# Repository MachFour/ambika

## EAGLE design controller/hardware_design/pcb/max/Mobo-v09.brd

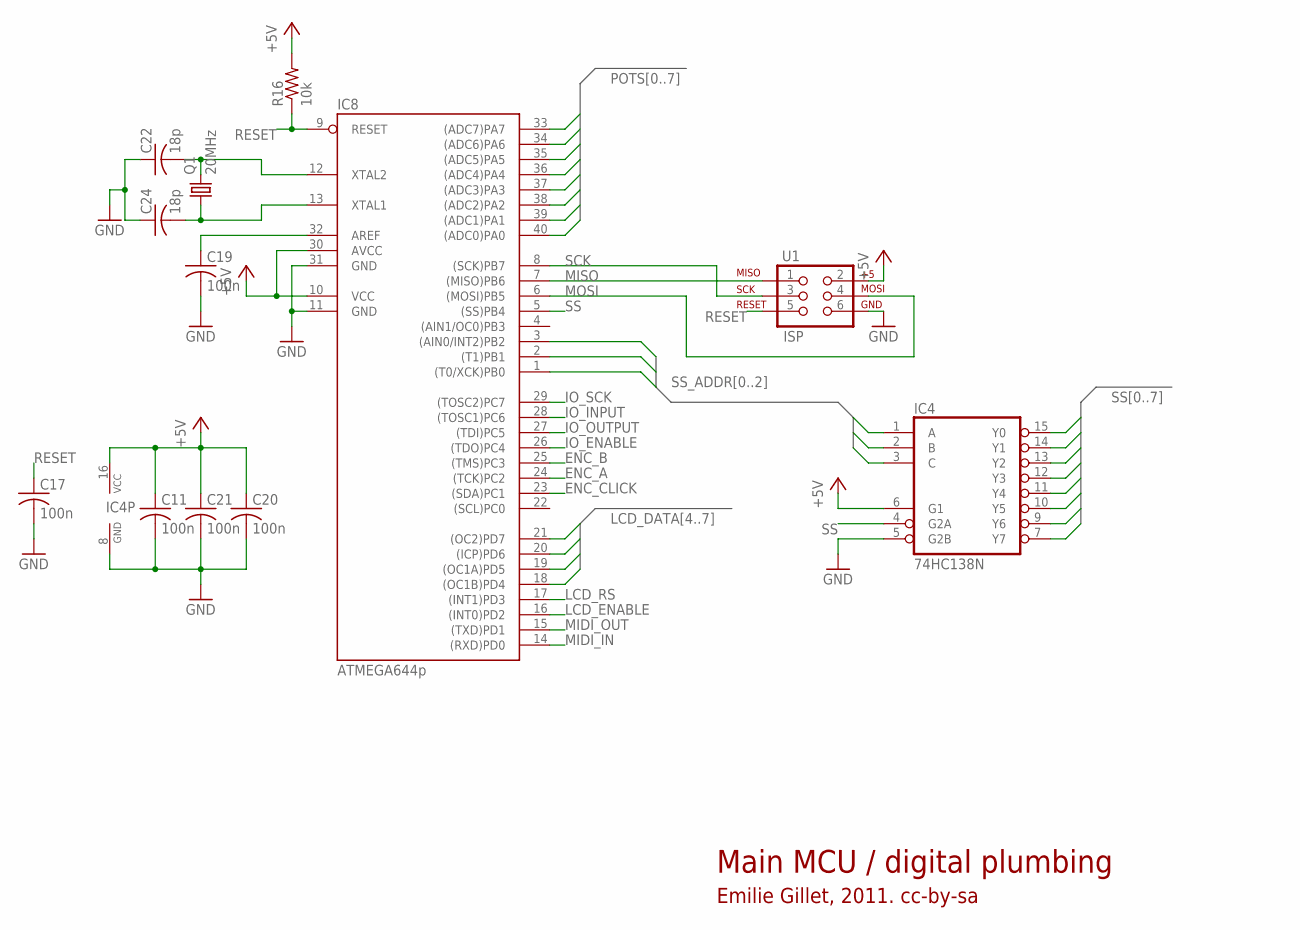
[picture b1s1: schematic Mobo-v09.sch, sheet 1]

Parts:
C11, C17, C19, C20, C21: 100n; C025-024X044
C22, C24: 18p; C025-024X044
IC4: 74HC138N; DIL16
IC8: ATMEGA644p; DIL40
Q1: 20MHz; HC49U-V
R16: 10k; 0204/7
U1: ISP; 2X3

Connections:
+5V: C11.1, C20.1, C21.1, IC4.6 (G1), IC4.16 (VCC), IC8.10 (VCC), IC8.30 (AVCC), R16.2, U1.2; also elsewhere on the board
ENC_A: IC8.24 ((TCK)PC2); also elsewhere on the board
ENC_B: IC8.25 ((TMS)PC3); also elsewhere on the board
ENC_CLICK: IC8.23 ((SDA)PC1); also elsewhere on the board
GND: C11.2, C17.2, C19.2, C20.2, C21.2, C22.1, C24.1, IC4.5 (G2B), IC4.8 (GND), IC8.11 (GND), IC8.31 (GND), U1.6; also elsewhere on the board
IO_ENABLE: IC8.26 ((TDO)PC4); also elsewhere on the board
IO_INPUT: IC8.28 ((TOSC1)PC6); also elsewhere on the board
IO_OUTPUT: IC8.27 ((TDI)PC5); also elsewhere on the board
IO_SCK: IC8.29 ((TOSC2)PC7); also elsewhere on the board
LCD_DATA4: IC8.18 ((OC1B)PD4); also elsewhere on the board
LCD_DATA5: IC8.19 ((OC1A)PD5); also elsewhere on the board
LCD_DATA6: IC8.20 ((ICP)PD6); also elsewhere on the board
LCD_DATA7: IC8.21 ((OC2)PD7); also elsewhere on the board
LCD_ENABLE: IC8.16 ((INT0)PD2); also elsewhere on the board
LCD_RS: IC8.17 ((INT1)PD3); also elsewhere on the board
MIDI_IN: IC8.14 ((RXD)PD0); also elsewhere on the board
MIDI_OUT: IC8.15 ((TXD)PD1); also elsewhere on the board
MISO: IC8.7 ((MISO)PB6), U1.1; also elsewhere on the board
MOSI: IC8.6 ((MOSI)PB5), U1.4; also elsewhere on the board
unnamed: C19.1, IC8.32 (AREF)
unnamed: C24.2, IC8.13 (XTAL1), Q1.1
unnamed: C22.2, IC8.12 (XTAL2), Q1.2
POTS0: IC8.40 ((ADC0)PA0); also elsewhere on the board
POTS1: IC8.39 ((ADC1)PA1); also elsewhere on the board
POTS2: IC8.38 ((ADC2)PA2); also elsewhere on the board
POTS3: IC8.37 ((ADC3)PA3); also elsewhere on the board
POTS4: IC8.36 ((ADC4)PA4); also elsewhere on the board
POTS5: IC8.35 ((ADC5)PA5); also elsewhere on the board
POTS6: IC8.34 ((ADC6)PA6); also elsewhere on the board
POTS7: IC8.33 ((ADC7)PA7); also elsewhere on the board
RESET: C17.1, IC8.9 (RESET), R16.1, U1.5
SCK: IC8.8 ((SCK)PB7), U1.3; also elsewhere on the board
SS: IC4.4 (G2A), IC8.5 ((SS)PB4)
SS0: IC4.15 (Y0); also elsewhere on the board
SS1: IC4.14 (Y1); also elsewhere on the board
SS2: IC4.13 (Y2); also elsewhere on the board
SS3: IC4.12 (Y3); also elsewhere on the board
SS4: IC4.11 (Y4); also elsewhere on the board
SS5: IC4.10 (Y5); also elsewhere on the board
SS6: IC4.9 (Y6); also elsewhere on the board
SS7: IC4.7 (Y7); also elsewhere on the board
SS_ADDR0: IC4.1 (A), IC8.1 ((T0/XCK)PB0)
SS_ADDR1: IC4.2 (B), IC8.2 ((T1)PB1)
SS_ADDR2: IC4.3 (C), IC8.3 ((AIN0/INT2)PB2)

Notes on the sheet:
Main MCU / digital plumbing
Emilie Gillet, 2011. cc-by-sa

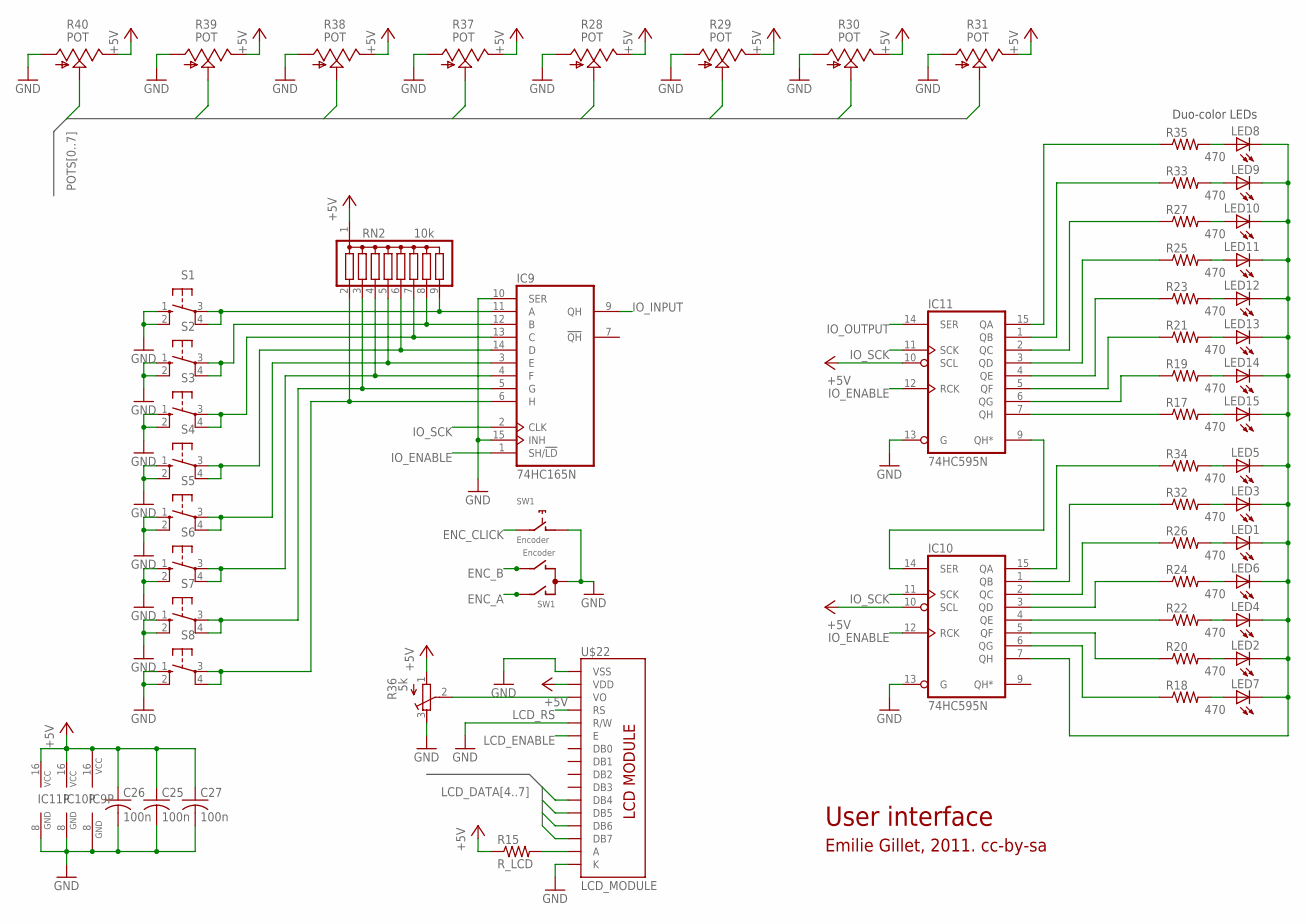
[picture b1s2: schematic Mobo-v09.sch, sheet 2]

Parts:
C25, C26, C27: 100n; C025-024X044
IC9: 74HC165N; DIL16
IC10, IC11: 74HC595N; DIL16
LED1, LED2, LED3, LED4, LED5, LED6, LED7, LED8, LED9, LED10, LED11, LED12, LED13, LED14, LED15: LED3MM
R15: R_LCD; 0204/7
R17, R18, R19, R20, R21, R22, R23, R24, R25, R26, R27, R32, R33, R34, R35: 470; 0204/7
R28, R29, R30, R31, R37, R38, R39, R40: POT; ALPS_POT_VERTICAL
R36: 5k; RTRIM3339P
RN2: 10k; SIL9
S1, S2, S3, S4, S5, S6, S7, S8: 40-XX; B3F-40XX
SW1: Encoder; ALPS_EC12E_SW
U$22: LCD_MODULE; LCD_MODULE_2X40

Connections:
+5V: C25.1, C26.1, C27.1, IC9.16 (VCC), IC10.10 (SCL), IC10.16 (VCC), IC11.10 (SCL), IC11.16 (VCC), R15.1, R28.P$1 (E), R29.P$1 (E), R30.P$1 (E), R31.P$1 (E), R36.1 (E), R37.P$1 (E), R38.P$1 (E), R39.P$1 (E), R40.P$1 (E), RN2.1, U$22.2 (VDD); also elsewhere on the board
ENC_A: SW1.A; also elsewhere on the board
ENC_B: SW1.B; also elsewhere on the board
ENC_CLICK: SW1.E (2); also elsewhere on the board
GND: C25.2, C26.2, C27.2, IC9.8 (GND), IC9.10 (SER), IC9.15 (INH), IC10.8 (GND), IC10.13 (G), IC11.8 (GND), IC11.13 (G), R28.P$3 (A), R29.P$3 (A), R30.P$3 (A), R31.P$3 (A), R36.3 (A), R37.P$3 (A), R38.P$3 (A), R39.P$3 (A), R40.P$3 (A), S1.1 (S), S1.2 (S1), S2.1 (S), S2.2 (S1), S3.1 (S), S3.2 (S1), S4.1 (S), S4.2 (S1), S5.1 (S), S5.2 (S1), S6.1 (S), S6.2 (S1), S7.1 (S), S7.2 (S1), S8.1 (S), S8.2 (S1), SW1.C, SW1.D (1), U$22.1 (VSS), U$22.5 (R/W), U$22.16 (K); also elsewhere on the board
IO_ENABLE: IC9.1 (SH/!LD), IC10.12 (RCK), IC11.12 (RCK); also elsewhere on the board
IO_INPUT: IC9.9 (QH); also elsewhere on the board
IO_OUTPUT: IC11.14 (SER); also elsewhere on the board
IO_SCK: IC9.2 (CLK), IC10.11 (SCK), IC11.11 (SCK); also elsewhere on the board
LCD_DATA4: U$22.11 (DB4); also elsewhere on the board
LCD_DATA5: U$22.12 (DB5); also elsewhere on the board
LCD_DATA6: U$22.13 (DB6); also elsewhere on the board
LCD_DATA7: U$22.14 (DB7); also elsewhere on the board
LCD_ENABLE: U$22.6 (E); also elsewhere on the board
LCD_RS: U$22.4 (RS); also elsewhere on the board
unnamed: IC11.2 (QC), R27.1
unnamed: IC9.3 (E), RN2.5, S5.3, S5.4 (P1)
unnamed: IC9.5 (G), RN2.3, S7.3, S7.4 (P1)
unnamed: IC9.4 (F), RN2.4, S6.3, S6.4 (P1)
unnamed: IC9.14 (D), RN2.6, S4.3, S4.4 (P1)
unnamed: R36.2 (S), U$22.3 (VO)
unnamed: IC9.11 (A), RN2.9, S1.3, S1.4 (P1)
unnamed: IC11.15 (QA), R35.1
unnamed: IC11.1 (QB), R33.1
unnamed: IC11.3 (QD), R25.1
unnamed: IC11.4 (QE), R23.1
unnamed: IC11.5 (QF), R21.1
unnamed: IC11.7 (QH), R17.1
unnamed: IC11.6 (QG), R19.1
unnamed: LED8.A, R35.2
unnamed: LED9.A, R33.2
unnamed: LED10.A, R27.2
unnamed: LED11.A, R25.2
unnamed: LED12.A, R23.2
unnamed: LED13.A, R21.2
unnamed: LED14.A, R19.2
unnamed: LED15.A, R17.2
unnamed: IC10.7 (QH), LED1.K (C), LED2.K (C), LED3.K (C), LED4.K (C), LED5.K (C), LED6.K (C), LED7.K (C), LED8.K (C), LED9.K (C), LED10.K (C), LED11.K (C), LED12.K (C), LED13.K (C), LED14.K (C), LED15.K (C)
unnamed: IC10.15 (QA), R34.1
unnamed: IC10.1 (QB), R32.1
unnamed: IC10.3 (QD), R24.1
unnamed: IC10.4 (QE), R22.1
unnamed: IC10.5 (QF), R20.1
unnamed: LED5.A, R34.2
unnamed: LED3.A, R32.2
unnamed: R15.2, U$22.15 (A)
unnamed: LED1.A, R26.2
unnamed: LED6.A, R24.2
unnamed: LED4.A, R22.2
unnamed: LED2.A, R20.2
unnamed: IC10.14 (SER), IC11.9 (QH*)
unnamed: IC9.12 (B), RN2.8, S2.3, S2.4 (P1)
unnamed: IC10.2 (QC), R26.1
unnamed: IC9.13 (C), RN2.7, S3.3, S3.4 (P1)
unnamed: IC9.6 (H), RN2.2, S8.3, S8.4 (P1)
unnamed: LED7.A, R18.2
unnamed: IC10.6 (QG), R18.1
POTS0: R40.P$2 (S); also elsewhere on the board
POTS1: R39.P$2 (S); also elsewhere on the board
POTS2: R38.P$2 (S); also elsewhere on the board
POTS3: R37.P$2 (S); also elsewhere on the board
POTS4: R28.P$2 (S); also elsewhere on the board
POTS5: R29.P$2 (S); also elsewhere on the board
POTS6: R30.P$2 (S); also elsewhere on the board
POTS7: R31.P$2 (S); also elsewhere on the board

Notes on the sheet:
User interface
Duo-color LEDs
Emilie Gillet, 2011. cc-by-sa

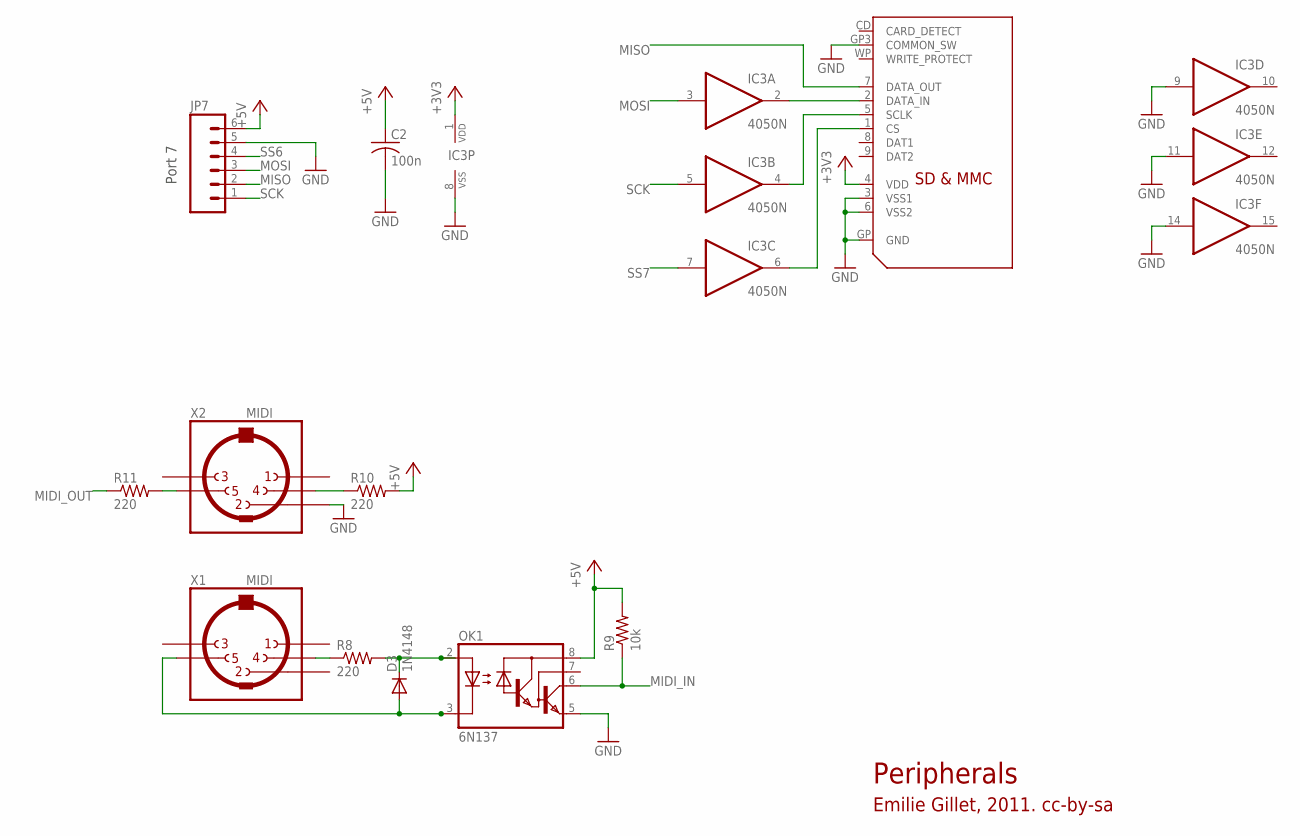
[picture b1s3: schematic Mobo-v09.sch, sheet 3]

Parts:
C2: 100n; C025-024X044
D3: 1N4148; D-5
IC3: 4050N; DIL16
JP7: M06SIP; 1X06
OK1: 6N137; DIL08
R8, R10, R11: 220; 0204/7
R9: 10k; 0204/7
U$26: SDMMC06132; 06132
X1, X2: MIDI; MAB5SH

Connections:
+3V3: IC3.1 (VDD), U$26.4 (VDD); also elsewhere on the board
+5V: C2.1, JP7.6, OK1.8 (VCC), R9.2, R10.2; also elsewhere on the board
GND: C2.2, IC3.8 (VSS), IC3.9 (I), IC3.11 (I), IC3.14 (I), JP7.5, OK1.5 (GND), U$26.3 (VSS1), U$26.6 (VSS2), U$26.GP (GND), U$26.GP3 (COMMON_SW), X2.2; also elsewhere on the board
MIDI_IN: OK1.6 (VO), R9.1; also elsewhere on the board
MIDI_OUT: R11.1; also elsewhere on the board
MISO: JP7.2, U$26.7 (DATA_OUT); also elsewhere on the board
MOSI: IC3.3 (I), JP7.3; also elsewhere on the board
MOSI_3V3: IC3.2 (O), U$26.2 (DATA_IN)
unnamed: R11.2, X2.5
unnamed: D3.C, OK1.2 (A), R8.2
unnamed: R10.1, X2.4
unnamed: R8.1, X1.4
unnamed: D3.A, OK1.3 (C), X1.5
SCK: IC3.5 (I), JP7.1; also elsewhere on the board
SCK_3V3: IC3.4 (O), U$26.5 (SCLK)
SS6: JP7.4; also elsewhere on the board
SS7: IC3.7 (I); also elsewhere on the board
SS7_3V3: IC3.6 (O), U$26.1 (CS)

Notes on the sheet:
Peripherals
Emilie Gillet, 2011. cc-by-sa
Port 7

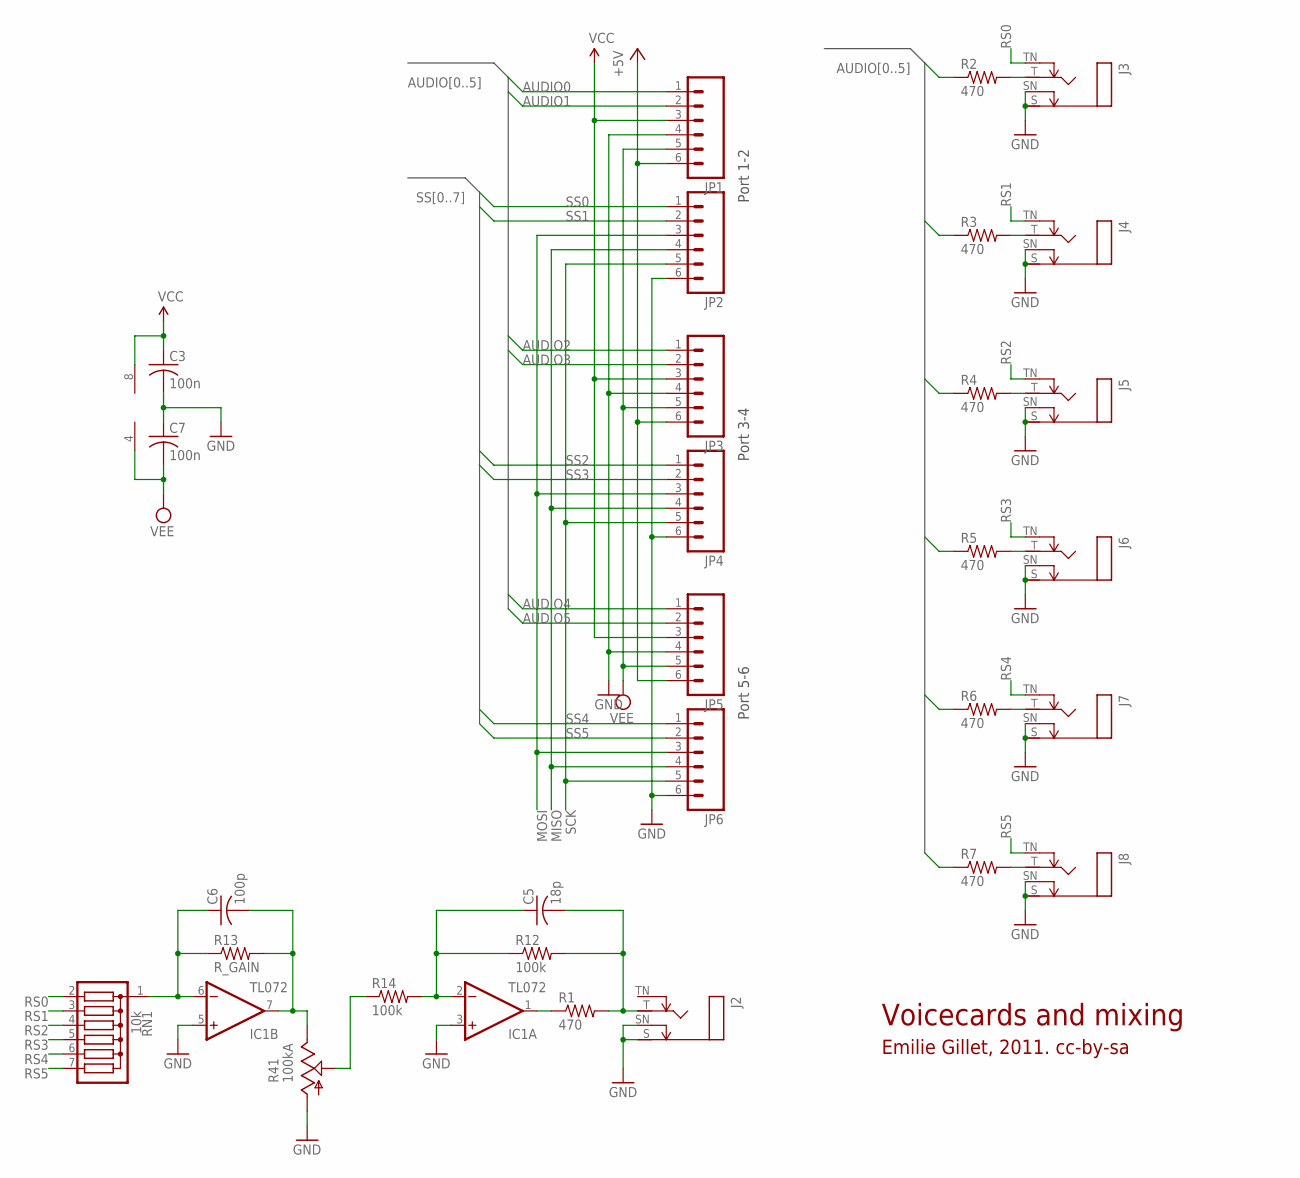
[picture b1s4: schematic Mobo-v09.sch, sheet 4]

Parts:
C3, C7: 100n; C025-024X044
C5: 18p; C025-024X044
C6: 100p; C025-024X044
IC1: TL072; DIL08
J2, J3, J4, J5, J6, J7, J8: MONOSWSLIM; NRJ4HF
JP1, JP2, JP3, JP4, JP5, JP6: M06SIP; 1X06
R1, R2, R3, R4, R5, R6, R7: 470; 0204/7
R12, R14: 100k; 0204/7
R13: R_GAIN; 0204/7
R41: 100kA; ALPS_POT_VERTICAL
RN1: 10k; SIL7

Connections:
+5V: JP1.6, JP3.6, JP5.6; also elsewhere on the board
AUDIO0: JP1.1, R2.1
AUDIO1: JP1.2, R3.1
AUDIO2: JP3.1, R4.1
AUDIO3: JP3.2, R5.1
AUDIO4: JP5.1, R6.1
AUDIO5: JP5.2, R7.1
GND: C3.2, C7.1, IC1.3 (+IN), IC1.5 (+IN), J2.S, J2.SN, J3.S, J3.SN, J4.S, J4.SN, J5.S, J5.SN, J6.S, J6.SN, J7.S, J7.SN, J8.S, J8.SN, JP1.4, JP2.6, JP3.4, JP4.6, JP5.4, JP6.6, R41.P$3 (A); also elsewhere on the board
MISO: JP2.4, JP4.4, JP6.4; also elsewhere on the board
MOSI: JP2.3, JP4.3, JP6.3; also elsewhere on the board
unnamed: C6.2, IC1.7 (OUT), R13.2, R41.P$1 (E)
unnamed: C6.1, IC1.6 (-IN), R13.1, RN1.1
unnamed: R14.1, R41.P$2 (S)
unnamed: C5.1, IC1.2 (-IN), R12.1, R14.2
unnamed: C5.2, J2.T, R1.2, R12.2
unnamed: J3.T, R2.2
unnamed: J4.T, R3.2
unnamed: J5.T, R4.2
unnamed: J6.T, R5.2
unnamed: J7.T, R6.2
unnamed: J8.T, R7.2
unnamed: IC1.1 (OUT), R1.1
RS0: J3.TN, RN1.2
RS1: J4.TN, RN1.3
RS2: J5.TN, RN1.4
RS3: J6.TN, RN1.5
RS4: J7.TN, RN1.6
RS5: J8.TN, RN1.7
SCK: JP2.5, JP4.5, JP6.5; also elsewhere on the board
SS0: JP2.1; also elsewhere on the board
SS1: JP2.2; also elsewhere on the board
SS2: JP4.1; also elsewhere on the board
SS3: JP4.2; also elsewhere on the board
SS4: JP6.1; also elsewhere on the board
SS5: JP6.2; also elsewhere on the board
VCC: C3.1, IC1.8 (V+), JP1.3, JP3.3, JP5.3; also elsewhere on the board
VEE: C7.2, IC1.4 (V-), JP1.5, JP3.5, JP5.5; also elsewhere on the board

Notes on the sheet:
Voicecards and mixing
Emilie Gillet, 2011. cc-by-sa
Port 1-2
Port 3-4
Port 5-6

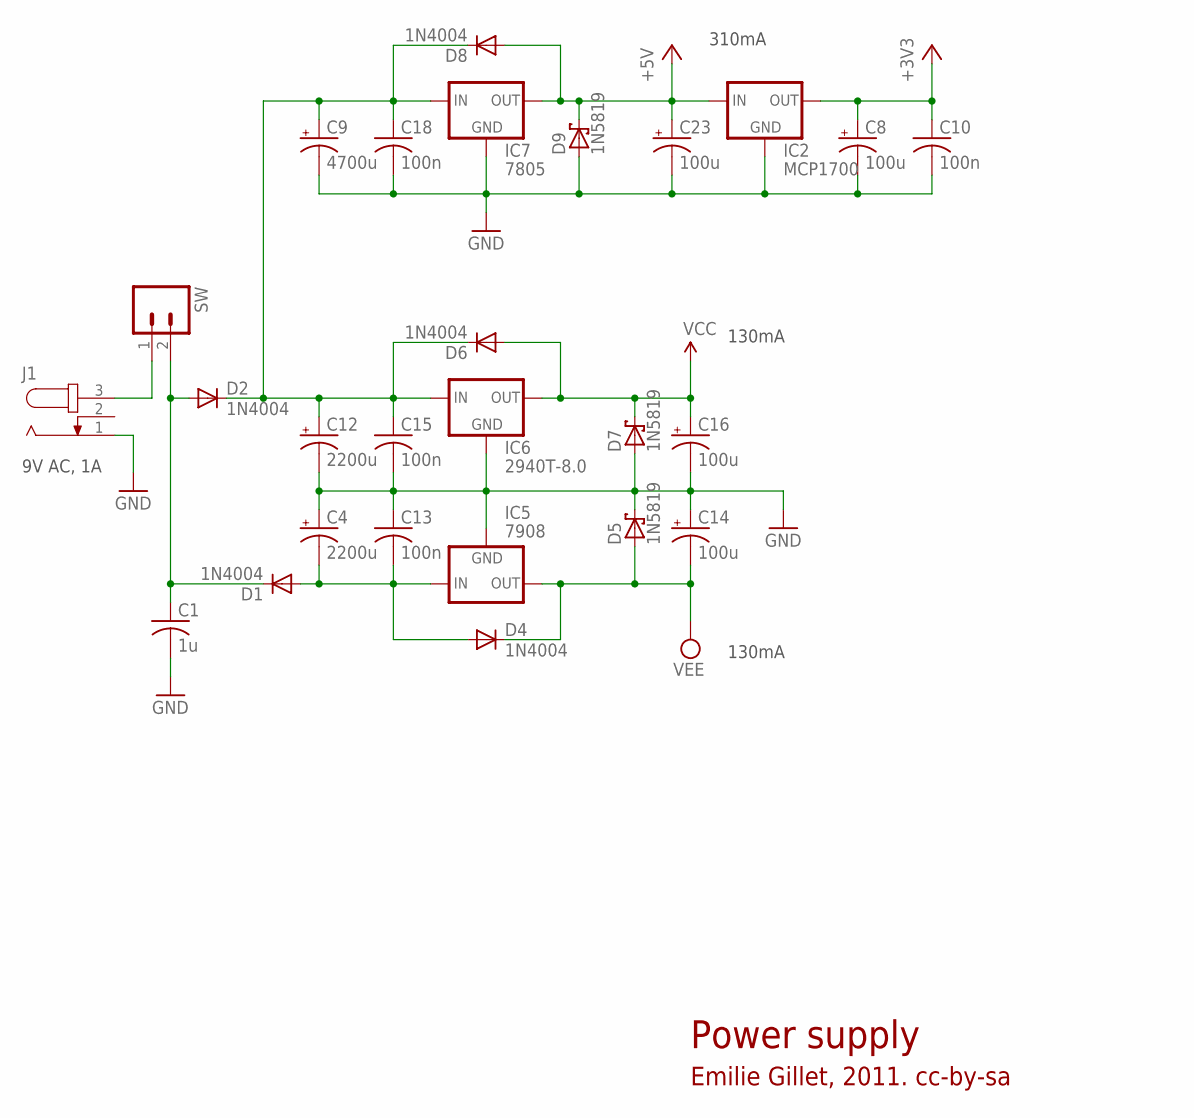
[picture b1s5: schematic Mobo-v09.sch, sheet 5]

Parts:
C1: 1u; C075-052X106
C4, C12: 2200u; E5-13
C8, C14, C16, C23: 100u; E2,5-7
C9: 4700u; E7,5-16
C10: 100n; C025-024X044
C13, C15, C18: 100n; C025-025X050
D1, D2, D4, D6, D8: 1N4004; DO41-10
D5, D7, D9: 1N5819; DO41-7.6
IC2: MCP1700; TO92-INLINE
IC5: 7908; 79XXL
IC6: 2940T-8.0; 78XXL
IC7: 7805; 78XXL
J1: JACK-PLUG2; SPC4078_BIG_HOLES
SW: M02PTH; 1X02

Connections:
+3V3: C8.+, C10.1, IC2.3 (OUT); also elsewhere on the board
+5V: C23.+, D8.A, D9.C, IC2.2 (IN), IC7.OUT; also elsewhere on the board
GND: C1.2, C4.+, C8.-, C9.-, C10.2, C12.-, C13.1, C14.+, C15.2, C16.-, C18.2, C23.-, D5.C, D7.A, D9.A, IC2.1 (GND), IC5.GND, IC6.GND, IC7.GND, J1.1; also elsewhere on the board
unnamed: J1.3, SW.1
unnamed: C4.-, C13.2, D1.A, D4.A, IC5.IN
unnamed: C9.+, C12.+, C15.1, C18.1, D2.C, D6.C, D8.C, IC6.IN, IC7.IN
unnamed: C1.1, D1.C, D2.A, SW.2
VCC: C16.+, D6.A, D7.C, IC6.OUT; also elsewhere on the board
VEE: C14.-, D4.C, D5.A, IC5.OUT; also elsewhere on the board

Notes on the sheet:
9V AC, 1A
Power supply
Emilie Gillet, 2011. cc-by-sa
130mA
310mA

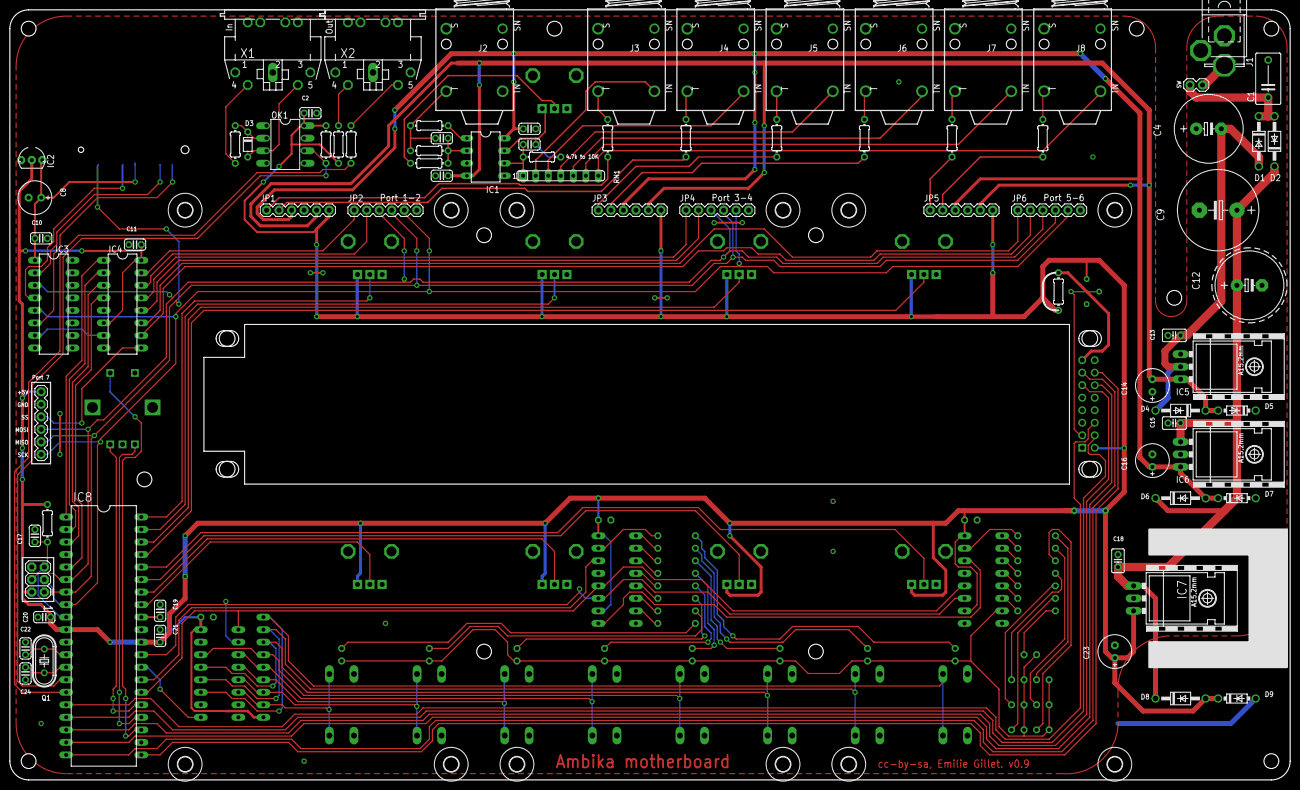
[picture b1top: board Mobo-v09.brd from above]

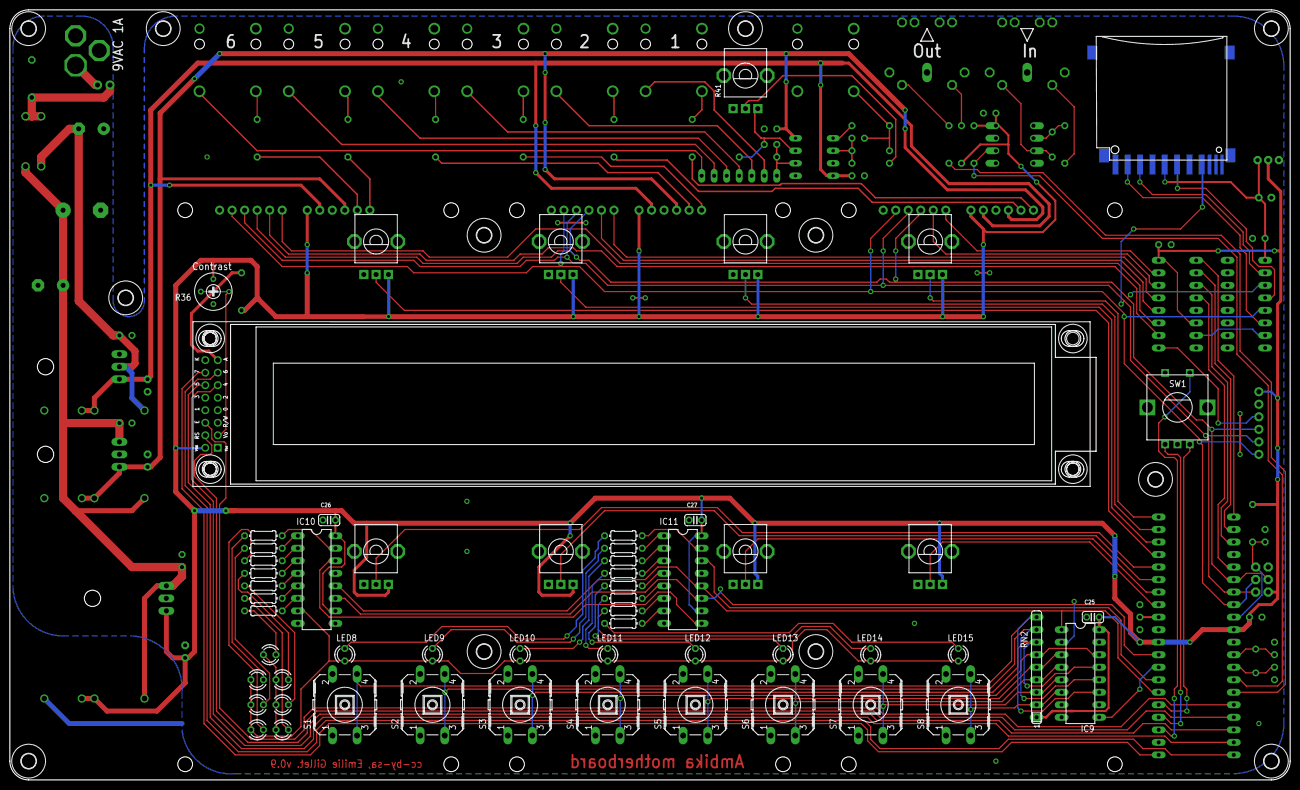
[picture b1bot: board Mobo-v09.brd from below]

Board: 2 copper layers, 259.6 x 156.1 mm, 165 parts (70 on the bottom side), 125 nets.

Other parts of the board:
U$1: V2_LOGO
U$2, U$3, U$4, U$5, U$6, U$7, U$11, U$12, U$13, U$14, U$15, U$16, U$17, U$18, U$19, U$20, U$21, U$23, U$24, U$25, U$27, U$28, U$29, U$30: 3,0
U$8, U$9, U$10: D02A-L

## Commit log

2020-03-22 fixed for compilation with GCC 8+, refactoring, voicecards not fully working yet
2020-03-23 reworking of major data structures to use safer pointer code, reduce clang-tidy warnings
2020-03-25 more refactoring
2020-03-28 Controller partway though refactor, voicecard not quite working...
2020-03-29 fix stupid bugs, improved variable naming
2020-03-29 refactoring of variable names and computations, still can't find the final bug...
2020-04-16 minor refactoring
2020-04-16 fixed bug in triangle reso, commented some stuff
2020-04-17 minor refactorings on voicecard
2020-04-18 Controller refactor in a seemingly workable state
2020-04-18 celebrate things working with a version bump
2020-04-18 squash some final warnings, minor refactoring
2020-04-18 patches behaving a little weird, more refactoring
2020-04-18 fixed a bug in library.cc, more refactoring
2020-04-18 fixed LFO bugs, enum refactoring
2020-04-23 remove execute bit
2020-04-25 refactor of controller data structures
2020-05-02 added combined renderCsResoWave function, random refactorings
2020-05-02 ported Phase57 mods
2020-05-07 initial commit of polyblep waves and updated resource generation files
2020-05-14 use uint24_t for phase counters, work on polyblep (commented out) and other tweaks
2020-05-22 changed FM synthesis waveforms
2020-08-29 fixed bug in performance page caused by incomplete refactoring

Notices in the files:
controller/hardware_design/pcb/max/Mobo-v09.brd:
cc-by-sa, Emilie Gillet. v0.9
